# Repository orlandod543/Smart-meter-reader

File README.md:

# **P1 Reader Board for Smart Meters**

This is a P1 reader board that I built to measure electricity and gas from smart meters typically found in the Netherlands. It is designed to be a simple, DIY alternative to commercially available devices, fully compatible with Home Assistant and ESPHome, while being easy to assemble at home.

## **Key Features**
- **Powered directly by the smart meter**: No external power supply is needed; the board is powered from the P1 port of your meter.
- **Wi-Fi Connectivity**: The board connects to your local network via Wi-Fi.
- **Home Assistant Integration**: The design is fully compatible with Home Assistant for easy monitoring and automation.
- **ESPHome Compatibility**: It uses the DSMR (Dutch Smart Meter Requirements) component of ESPHome for simple configuration.
- **Easy DIY Assembly**: The PCB is designed for ease of assembly, allowing you to solder it at home in a few hours.

Additionally, the board includes an optional **DHT22 sensor** to monitor the temperature and humidity inside your electrical cabinet.

At the moment an example of the script to be used is not in this repository. Please go to https://esphome.io/components/sensor/dsmr.html for more details on how to create it. 

## **Getting Started**
- Assemble the PCB using the provided schematics.
- Create a ESPHome script following the instructions here: https://esphome.io/components/sensor/dsmr.html
- Flash the ESPHome firmware with your network details.
- Integrate with Home Assistant or any other compatible home automation platform.

## **License Information**

This hardware design is licensed under the **CERN Open Hardware License Strongly Reciprocal (CERN-OHL-S) v2.0**. This ensures that all modifications and derivative works are shared under the same open-source terms.

### **Summary of License Terms**
1. **You are free to**:
   - Use the design files for any purpose.
   - Modify the design, as long as you share your modifications under the same license.
   - Manufacture products based on this design.

2. **Conditions**:
   - You must give appropriate credit, including a link to the original design and this license.
   - If you modify the design and distribute the modified work (either as hardware or design files), you must share the modifications under the same license.

3. **Limitations**:
   - This license ensures that any modifications or derivatives of this design remain open-source.

For the full terms, please refer to the LICENSE.txt file.

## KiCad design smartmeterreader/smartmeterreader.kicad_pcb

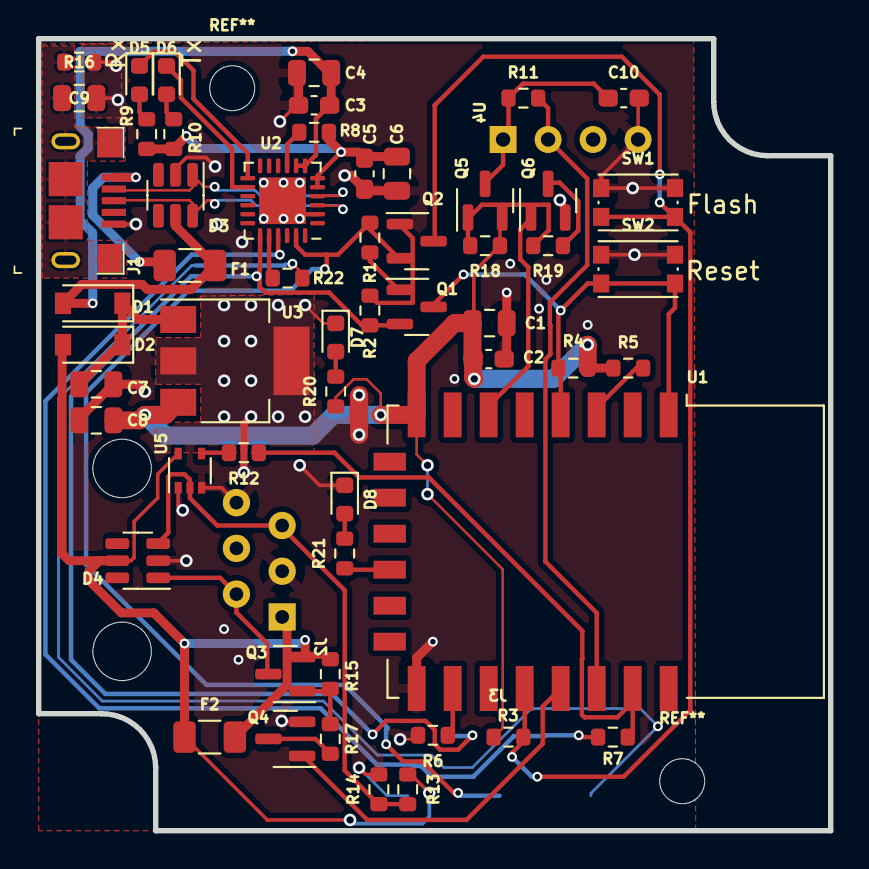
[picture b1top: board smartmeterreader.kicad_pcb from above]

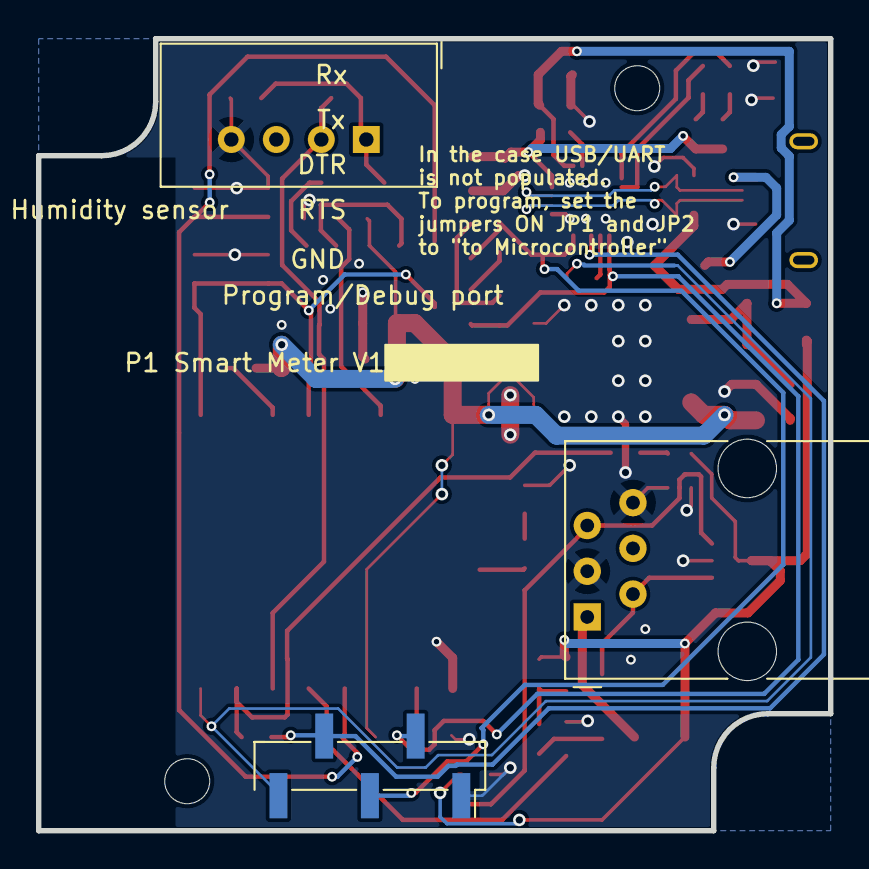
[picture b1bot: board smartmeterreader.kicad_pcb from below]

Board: 4 copper layers, 44.0 x 44.0 mm, 58 parts (3 on the bottom side), 42 nets.

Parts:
C1, C7, C8: 10uF; C_0805_2012Metric
C2, C3, C5: 100nF; C_0603_1608Metric_Pad1.08x0.95mm_HandSolder
C4, C6: 4.7uF; C_0805_2012Metric
C9: 4.7nF_250V; C_0805_2012Metric
C10: 1uF; C_0603_1608Metric_Pad1.08x0.95mm_HandSolder
D1, D2: PMEG2010ER; D_SOD-123
D3, D4: RCLAMP0504S; SOT-23-6
D5, D6, D7, D8: Green; LED_0603_1608Metric
F1, F2: 1A; Fuse_1206_3216Metric
J1: USB_B_Micro_RA; USB_Micro_B_Female_10118193-0001LF
J2: RJ12; RJ12_Amphenol_54601
J3: 1X05pin_2.54mm_smd; PinHeader_1x05_P2.54mm_Vertical_SMD_Pin1Right
Q1, Q2, Q4, Q6: 2N7002NXBK; SOT-23
Q3, Q5: PMV75UP; SOT-23
R1, R2, R3, R4, R5, R6, R11, R12, R13, R15, R18: 10K; R_0603_1608Metric
R7, R17, R19, R22: 100R; R_0603_1608Metric
R8, R9, R10, R20, R21: 1K; R_0603_1608Metric
R14: 15K; R_0603_1608Metric
R16: 1M; R_0603_1608Metric
SW1, SW2: SPST_NO; SW_Push_1P1T_NO_CK_KMR2
U1: ESP-12F; ESP-12E
U2: CP2102N-A02-GQFN24; QFN-24-1EP_4x4mm_P0.5mm_EP2.6x2.6mm
U3: MCP1824S-3V3; SOT-223-3_TabPin2
U4: DHT22; DHT22_7.7x15.1_P2mm
U5: 74HC1G02GW; SOT-353_SC-70-5

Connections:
+3V3: C1.1, C2.1, C8.1, Q5.2 (S), R3.1, R4.1, R5.1, R18.1, R20.1, U1.8 (VCC), U3.3 (Vout)
/5V_USB: C3.1, C4.1, D1.2 (A), D3.5 (K5), F1.2, U2.7 (VREGIN), U2.8 (VBUS)
/5V_meter: D2.2 (A), D4.5 (K5), F2.1, Q3.2 (S), R13.1, R15.1, U5.5 (VCC)
/D+: D3.6 (K6), J1.3 (D+), U2.3 (D+)
/D-: D3.1 (K1), J1.2 (D-), U2.4 (D-)
/DATA_LINE: D4.3 (K3), J2.5, R13.2, R14.1, U5.2 (A)
/DATA_REQ: D4.1 (K1), J2.2, Q3.3 (D)
/DHT22_DATA: R11.2, U1.20 (GPIO5), U4.2 (Data)
/DHT22_EN: Q6.1 (G), U1.6 (GPIO12)
/Data_Req_TTL: Q4.1 (G), U1.19 (GPIO4)
/Data_line_TTL: R7.1, R12.1, U1.21 (GPIO3/RXD)
/GPIO0: Q2.3 (D), R3.2, SW1.2 (B), U1.18 (GPIO0)
/High_side_SW.sch/VOut: C10.1, Q5.3 (D), R11.1, U4.1 (VDD)
/Power_supply_LDO_3V3/Vin: C7.1, D1.1 (K), D2.1 (K), U3.1 (Vin)
/UART_DTR: J3.3, Q2.2 (S), R1.2, U2.23 (DTR)
/UART_RTS: J3.2, Q1.2 (S), R2.2, U2.19 (RTS)
/UART_RX: J3.5, R22.2, U1.22 (GPIO1/TXD)
/UART_TX: J3.4, R7.2, U2.21 (TXD)
/USB-UART-transceiver/3.3V: C5.1, C6.1, R8.1, R9.1, R10.1, U2.5 (VIO), U2.6 (VDD)
/USB-UART-transceiver/UART_RX: R22.1, U2.20 (RXD)
/nRST: Q1.3 (D), R4.2, SW2.2 (B), U1.1 (~RST), U1.4 (GPIO16)
Earth: C9.1, J1.SH (Shield), R16.1
GND: C1.2, C2.2, C3.2, C4.2, C5.2, C6.2, C7.2, C8.2, C9.2, C10.2, D3.2 (A), D4.2 (A), D7.1 (K), D8.1 (K), J1.5 (GND), J2.3, J2.6, J3.1, Q4.2 (S), Q6.2 (S), R6.2, R14.2, R16.2, SW1.1 (A), SW2.1 (A), U1.15 (GND), U2.2 (GND), U2.25 (GND), U3.2 (GND), U4.4 (GND), U5.1 (B), U5.3 (GND)
unnamed: D5.1 (K), U2.13 (GPIO.1/RXT)
unnamed: D5.2 (A), R9.2
unnamed: D6.1 (K), U2.14 (GPIO.0/TXT)
unnamed: D6.2 (A), R10.2
unnamed: D7.2 (A), R20.2
unnamed: D8.2 (A), R21.2
unnamed: F1.1, J1.1 (VBUS)
unnamed: F2.2, J2.1
unnamed: Q1.1 (G), R1.1
unnamed: Q2.1 (G), R2.1
unnamed: Q3.1 (G), R15.2, R17.1
unnamed: Q4.3 (D), R17.2
unnamed: Q5.1 (G), R18.2, R19.1
unnamed: Q6.3 (D), R19.2
unnamed: R5.2, U1.3 (EN)
unnamed: R6.1, U1.16 (GPIO15)
unnamed: R8.2, U2.9 (~RSTb)
unnamed: R12.2, U5.4 (Y)
unnamed: R21.1, U1.12 (GPIO10)

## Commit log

2021-12-13 Add P1 specification documentation
2021-12-13 Draft design
2021-12-16 Add gitignore file
2021-12-16 Initial version of the smart meter. -Needs compoonent review, - Needs schematics review - No layout
2022-09-24 Sync PCB with schematics
2022-10-15 Add datasheet of the proposed box to be used with the meter
2022-10-15 Add .zip to the gitignore list
2024-10-20 Add readme, licensing and a little bit more information about the case
2024-10-20 modified README
